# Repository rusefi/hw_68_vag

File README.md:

# hw_68_vag

[Forum Thread](https://rusefi.com/forum/viewtopic.php?f=4&t=1725)

https://github.com/rusefi/rusefi/tree/master/hardware/966595-1_and_963356-1-connector meets https://rusefi.com/forum/viewtopic.php?f=3&t=699

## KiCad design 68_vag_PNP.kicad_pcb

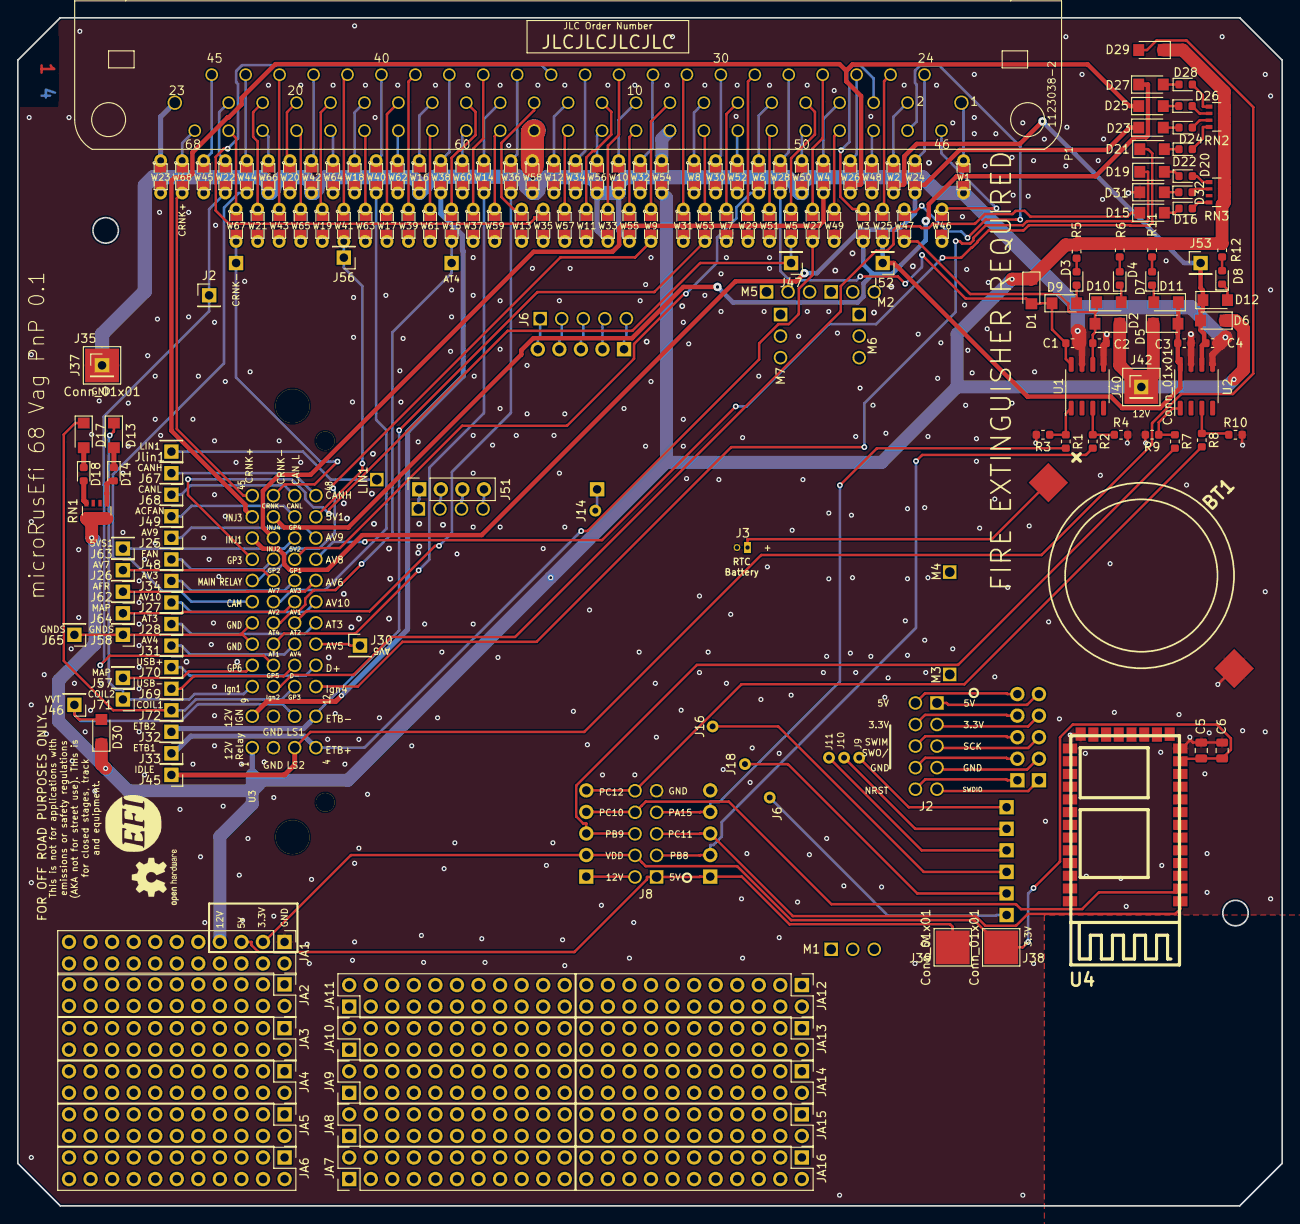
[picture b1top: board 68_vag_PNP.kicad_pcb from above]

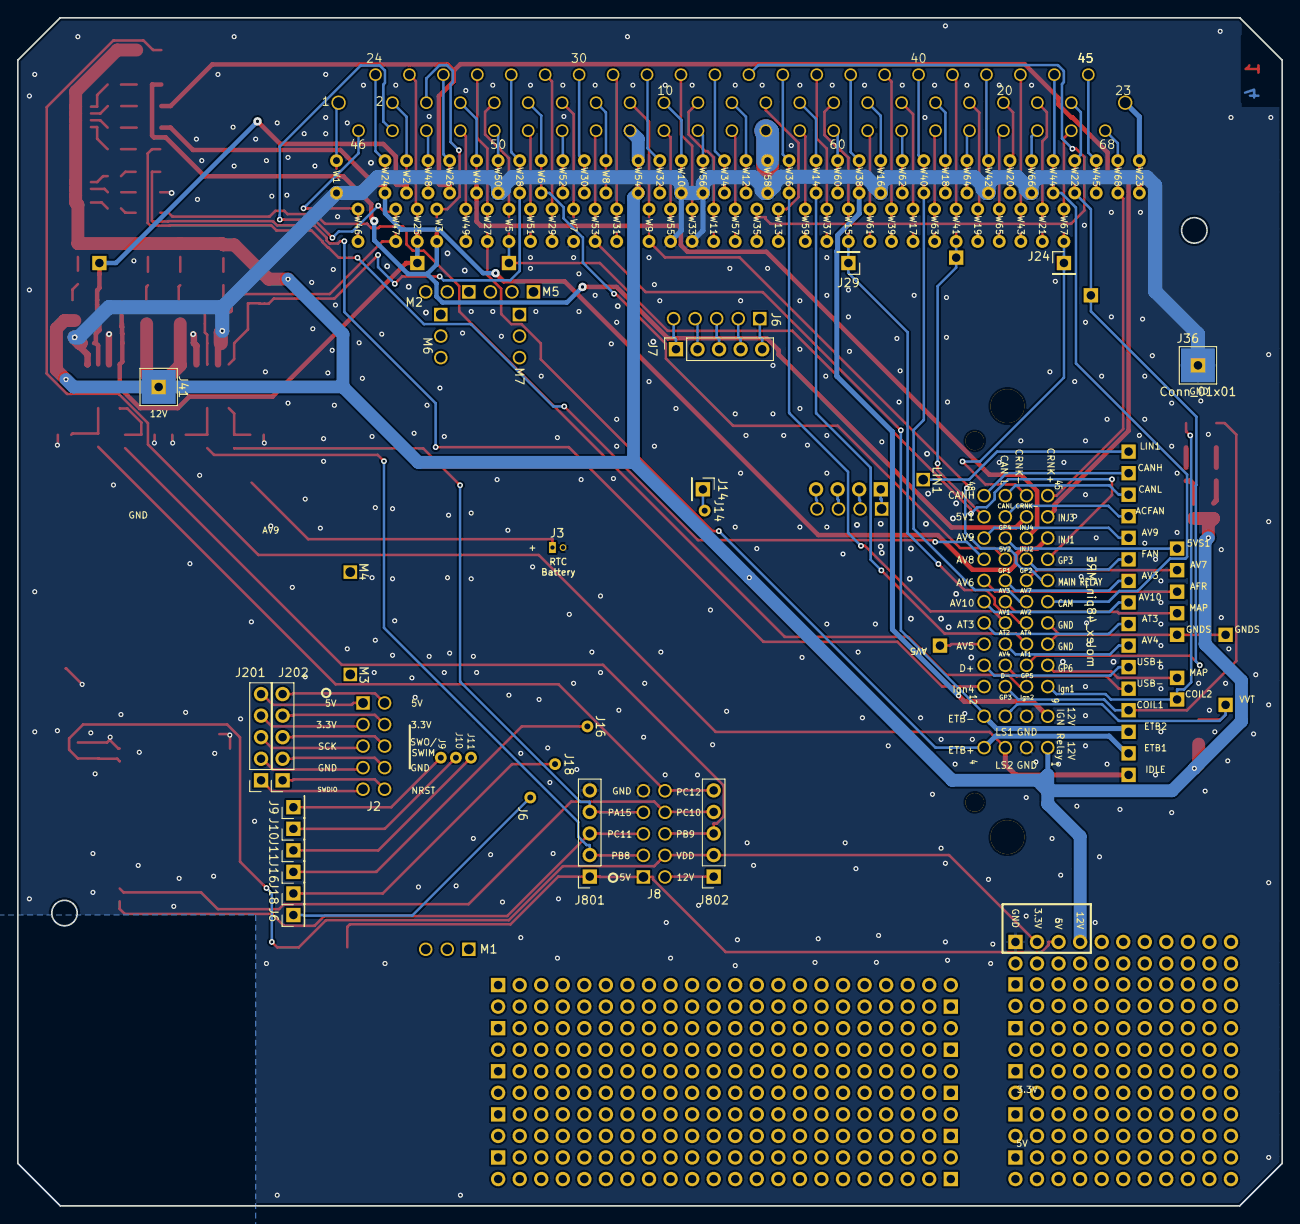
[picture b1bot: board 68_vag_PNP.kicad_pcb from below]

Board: 2 copper layers, 149.0 x 140.0 mm, 201 parts (16 on the bottom side), 185 nets.

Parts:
BT1: Battery_Cell; BATT_CR2032_MPD
C1, C2, C3, C4: 6.8n; C_0603_1608Metric
C5: 0.1u; C_0805_2012Metric
C6: 1u; C_0805_2012Metric
D1, D2, D5, D6, D9, D10, D11, D12, D13, D15, D17, D19, D21, D23, D25, D27, D29, D30, D31: D_Schottky; D_SMF
D3, D4, D7, D8, D14, D16, D18, D20, D22, D24, D26, D28, D32: LED; LED_0603_1608Metric
G1: Disclaimer; Off_Road_Disclaimer
J2, J6, J9, J10, J11, J14, J16, J18, J24, J25, J26, J27, J28, J29, J30, J31, J32, J33, J34, J35, J42, J45, J46, J47, J48, J49, J52, J53, J56, J57, J58, J62, J63, J64, J65, J67, J68, J69, J70, J71, J72: Conn_01x01; PinHeader_1x01_P2.54mm_Vertical
J7, J201, J202, J801, J802: Conn_01x05; PinSocket_1x05_P2.54mm_Vertical
J36, J37, J38, J39, J40, J41: Conn_01x01; TestPoint_Pad_4.0x4.0mm
J51: Conn_01x05; PinSocket_1x04_P2.54mm_Vertical
JA1, JA2, JA3, JA4, JA5, JA6, JA7, JA8, JA9, JA10, JA11, JA12, JA13, JA14, JA15, JA16: Conn_02x11_Odd_Even; PinHeader_2x11_P2.54mm_Vertical
Jlin1: Conn_01x01; PinHeader_1x01_P2.54mm_Vertical
LOGO1: LOGO
LOGO2: LOGO; JLC_PCB_TAG
LOGO3: LOGO; OSHW-Logo2_7.3x6mm_SilkScreen
P1: 1123038-2; 963356-1
R1, R2, R5, R6, R7, R8, R11, R12: 1k; R_0603_1608Metric
R3, R4, R9, R10: 10k; R_0603_1608Metric
RN1, RN2, RN3: 10k; R_Array_Convex_4x0603
U1, U2: VNLD5090; SO-8_3.9x4.9mm_P1.27mm
U3: molex_48pin_MRE; Molex_48_MRE
U4: ITEAD_HC-05
W1, W2, W3, W4, W5, W6, W7, W8, W9, W10, W11, W12, W13, W14, W15, W16, W17, W18, W19, W20, W21, W22, W23, W24, W25, W26, W27, W28, W29, W30, W31, W32, W33, W34, W35, W36, W37, W38, W39, W40, W41, W42, W43, W44, W45, W46, W47, W48, W49, W50, W51, W52, W53, W54, W55, W56, W57, W58, W59, W60, W61, W62, W63, W64, W65, W66, W67, W68: TestPoint_2Pole; SM0805_jumper

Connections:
+12V: D1.1, D2.1, D5.1, D6.1, D29.1, D30.1, J40.1, J41.1, J42.1, JA1.7, R5.2, R6.1, R11.2, R12.1, RN1.1, RN1.2, RN1.3, RN1.4, RN2.1, RN2.2, RN2.3, RN2.4, RN3.1, RN3.2, RN3.3, RN3.4, U3.1, W54.2
/5V_SENS1: J56.1, U3.44, W41.2
/5V_SENS2: J63.1, U3.39
/12_IGN_KEY: U3.5, W38.2
/AC_FAN: J49.1, U3.43
/AFR: J62.1, U3.32
/ALTERNATOR: J57.1, U3.13
/AT3_UNUSED: J28.1, U3.24
/AT4: J29.1, U3.22, W15.2
/AV3_UNUSED: J34.1, U3.31
/AV4_UNUSED: J31.1, U3.19
/AV5_UNUSED: J30.1, U3.20
/AV7_UNUSED: J26.1, U3.30
/AV8_UNUSED: D21.1, U3.36
/AV9_UNUSED: J25.1, U3.40
/AV10_UNUSED: J27.1, U3.28
/CAM: U3.25, W44.2
/CAN_H: J67.1, U3.48
/CAN_L: J68.1, U3.47
/CLT: U3.18, W14.2
/COIL1: D13.1, J71.1, U3.9
/COIL2: D17.1, J72.1, U3.11
/CRANK+: U3.45, W68.2
/CRANK-: J24.1, U3.46, W67.2
/ETB1: J33.1, U3.4, W27.2
/ETB2: J32.1, U3.8, W53.2
/FAN: J48.1, U3.34
/FUEL_RELAY: U3.35, W6.2
/GND_SENS: J58.1, J65.1, U3.17, U3.21
/HI2_UNUSED: D15.1, U3.10
/HI4_UNUSED: D19.1, U3.12
/IAT: U3.23, W36.2
/IDLE: D29.2, J45.1, U3.3
/INJ1: D23.1, U3.37, W24.2
/INJ2: U3.38, W4.2
/INJ3: D25.1, U3.41, W26.2
/INJ4: D27.1, U3.42, W3.2
/INJ5: C3.1, D5.2, D11.1, J52.1, U2.8, W25.2
/INJ6: C4.1, D6.2, D12.1, J53.1, U2.6, W2.2
/J201: J201.5, U3.J201
/J202: J202.5, U3.J202
/J203: J201.4, U3.J203
/J204: J202.4, U3.J204
/J205: J201.3, U3.J205
/J206: J202.3, U3.J206
/J207: J201.2, U3.J207
/J208: J202.2, U3.J208
/J209: J201.1, U3.J209
/J210: J202.1, U3.J210
/J801_5V: J39.1, J801.1, JA1.5, U3.J801
/J802_12V: J802.1, U3.J802
/J803_PB8: J801.2, R2.2, U3.J803
/J804_3.3V: C5.2, C6.1, J38.1, J802.2, JA1.3, U3.J804, U4.12
/J805_PC11: J801.3, U3.J805, U4.1
/J806_PB9: J802.3, R7.2, U3.J806
/J807_PA15: J801.4, R1.2, U3.J807
/J808_PC10: J802.4, U3.J808, U4.2
/J810_PC12: J802.5, R8.2, U3.J810
/MAIN_RELAY_CONTROL: U3.29, W9.2
/MAP: J64.1, U3.27
/MIL: J47.1, U3.33, W5.2
/O2-1Heat: C1.1, D1.2, D9.1, U1.8, W28.2
/O2-2Heat: C2.1, D2.2, D10.1, U1.6, W47.2
/TACH: J2.1, U3.14, W22.2
/TPS: U3.26, W40.2
/USBD+: J70.1, U3.16
/USBD-: J69.1, U3.15
/VBAT: BT1.1, U3.J31
/VVT: D30.2, J46.1, U3.7
GND: BT1.2, C1.2, C2.2, C3.2, C4.2, C5.1, C6.2, D31.1, J35.1, J36.1, J37.1, J801.5, JA1.1, R3.2, R4.2, R9.2, R10.2, U1.5, U1.7, U2.5, U2.7, U3.2, U3.6, U3.J32, U3.J809, U4.13, U4.21, U4.22, W1.2, W7.2, W10.2, W16.2, W33.2, W42.2, W50.2, W55.2, W56.2, W58.2, W66.2
unnamed: D3.1, D9.2
unnamed: D3.2, R5.1
unnamed: D4.2, R6.2
unnamed: D7.2, R11.1
unnamed: D8.2, R12.2
unnamed: D4.1, D10.2
unnamed: D7.1, D11.2
unnamed: D8.1, D12.2
unnamed: D13.2, D14.1
unnamed: D14.2, RN1.5
unnamed: D15.2, D16.1
unnamed: D16.2, RN3.8
unnamed: D17.2, D18.1
unnamed: D18.2, RN1.8
unnamed: D19.2, D20.1
unnamed: D20.2, RN3.5
unnamed: D21.2, D22.1
unnamed: D22.2, RN2.8
unnamed: D23.2, D24.1
unnamed: D24.2, RN2.7
unnamed: D25.2, D26.1
unnamed: D26.2, RN2.6
unnamed: D27.2, D28.1
unnamed: D28.2, RN2.5
unnamed: D31.2, D32.1
unnamed: D32.2, RN3.6
unnamed: J6.1, U3.J6
unnamed: J7.1, U3.J65
unnamed: J7.2, U3.J64
unnamed: J7.3, U3.J63
unnamed: J7.4, U3.J62
unnamed: J7.5, U3.J61
unnamed: J9.1, U3.J9
unnamed: J10.1, U3.J10
unnamed: J11.1, U3.J11
unnamed: J14.1, U3.J14
unnamed: J16.1, U3.J16
unnamed: J18.1, U3.J18
unnamed: J51.1, U3.J51
unnamed: J51.2, U3.J52
unnamed: J51.3, U3.J53
unnamed: J51.4, U3.J54
unnamed: Jlin1.1, U3.LIN1
unnamed: P1.1, W1.1
unnamed: P1.2, W2.1
unnamed: P1.3, W3.1
unnamed: P1.4, W4.1
unnamed: P1.5, W5.1
unnamed: P1.6, W6.1
unnamed: P1.7, W7.1
unnamed: P1.8, W8.1
unnamed: P1.9, W9.1
unnamed: P1.10, W10.1
unnamed: P1.11, W11.1
unnamed: P1.12, W12.1
unnamed: P1.13, W13.1
unnamed: P1.14, W14.1
unnamed: P1.15, W15.1
unnamed: P1.16, W16.1
unnamed: P1.17, W17.1
unnamed: P1.18, W18.1
unnamed: P1.19, W19.1
unnamed: P1.20, W20.1
unnamed: P1.21, W21.1
unnamed: P1.22, W22.1
unnamed: P1.23, W23.1
unnamed: P1.24, W24.1
unnamed: P1.25, W25.1
unnamed: P1.26, W26.1
unnamed: P1.27, W27.1
unnamed: P1.28, W28.1
unnamed: P1.29, W29.1
unnamed: P1.30, W30.1
unnamed: P1.31, W31.1
unnamed: P1.32, W32.1
unnamed: P1.33, W33.1
unnamed: P1.34, W34.1
unnamed: P1.35, W35.1
unnamed: P1.36, W36.1
unnamed: P1.37, W37.1
unnamed: P1.38, W38.1
unnamed: P1.39, W39.1
unnamed: P1.40, W40.1
unnamed: P1.41, W41.1
unnamed: P1.42, W42.1
unnamed: P1.43, W43.1
unnamed: P1.44, W44.1
unnamed: P1.45, W45.1
unnamed: P1.46, W46.1
unnamed: P1.47, W47.1
unnamed: P1.48, W48.1
unnamed: P1.49, W49.1
unnamed: P1.50, W50.1
unnamed: P1.51, W51.1
unnamed: P1.52, W52.1
unnamed: P1.53, W53.1
unnamed: P1.54, W54.1
unnamed: P1.55, W55.1
unnamed: P1.56, W56.1
unnamed: P1.57, W57.1
unnamed: P1.58, W58.1
unnamed: P1.59, W59.1
unnamed: P1.60, W60.1
unnamed: P1.61, W61.1
unnamed: P1.62, W62.1
unnamed: P1.63, W63.1
unnamed: P1.64, W64.1
unnamed: P1.65, W65.1
unnamed: P1.66, W66.1
unnamed: P1.67, W67.1
unnamed: P1.68, W68.1
unnamed: R1.1, R3.1, U1.1
unnamed: R2.1, R4.1, U1.3
unnamed: R7.1, R9.1, U2.1
unnamed: R8.1, R10.1, U2.3

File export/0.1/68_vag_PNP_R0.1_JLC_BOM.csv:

Comment,Designator,Footprint,LCSC, LCSC, MFG,MFG#, Vend1,Vend1#
"Battery_Cell","BT1","rusEFI_Modules:BATT_CR2032_MPD",""
"6.8n","C1,C2,C3,C4","Capacitor_SMD:C_0603_1608Metric","","C1631","KE MET,C0603C682K1RACTU","DIGI,399-3187-1-ND"
"0.1u","C5","Capacitor_SMD:C_0805_2012Metric","","C49678","",""
"1u","C6","Capacitor_SMD:C_0805_2012Metric","","C28323","",""
"D_Schottky","D13,D15,D17,D19,D21,D23,D25,D27,D30,D29,D31,D1,D2,D9,D10,D5,D6,D11,D12","Diode_SMD:D_SMF","","C64898","DIODES_INC,SBR2U60S1F","DIGI,SBR2U60S1F-7DICT-ND"
"LED","D14,D18,D20,D22,D24,D26,D28,D16,D32,D4,D3,D8,D7","LED_SMD:LED_0603_1608Metric","","C2286","DIALIGHT,598-8010-107F","DIGI,350-2029-1-ND"
"Disclaimer","G1","rusEFI_Modules:Off_Road_Disclaimer",""
"Conn_01x01","J40,J39,J38,J37,J36,J41","TestPoint:TestPoint_Pad_4.0x4.0mm",""
"Conn_01x05","J51","Connector_PinSocket_2.54mm:PinSocket_1x04_P2.54mm_Vertical",""
"Conn_01x05","J7,J801,J802,J201,J202","Connector_PinSocket_2.54mm:PinSocket_1x05_P2.54mm_Vertical",""
"Conn_02x11_Odd_Even","JA1,JA2,JA3,JA4,JA5,JA6,JA7,JA8,JA9,JA10,JA11,JA12,JA13,JA14,JA15,JA16","Connector_PinHeader_2.54mm:PinHeader_2x11_P2.54mm_Vertical",""
"Conn_01x01","Jlin1,J24,J25,J26,J27,J28,J29,J30,J31,J32,J33,J34,J35,J2,J56,J45,J46,J47,J48,J49,J58,J71,J72,J62,J63,J64,J67,J68,J69,J70,J57,J65,J6,J18,J9,J10,J11,J16,J14,J53,J52,J42","Connector_PinHeader_2.54mm:PinHeader_1x01_P2.54mm_Vertical",""
"LOGO","LOGO1","rusEFI_Modules:LOGO",""
"LOGO","LOGO2","rusEFI_Modules:JLC_PCB_TAG",""
"LOGO","LOGO3","Symbol:OSHW-Logo2_7.3x6mm_SilkScreen",""
"1123038-2","P1","rusEFI_Modules:963356-1",""
"1k","R1,R2,R6,R5,R7,R8,R12,R11","Resistor_SMD:R_0603_1608Metric","","C21190","YAGEO,RC0603JR-071KL","DIGI,311-1.0KGRCT-ND"
"10k","R4,R3,R10,R9","Resistor_SMD:R_0603_1608Metric","","C25804","YAGEO,RC0603JR-0710KL","DIGI,311-10KGRCT-ND"
"10k","RN2,RN3,RN1","Resistor_SMD:R_Array_Convex_4x0603","","C29718","YAGEO,YC164-JR-0710KL","DIGI,YC164J-10KCT-ND"
"VNLD5090","U1,U2","Package_SO:SO-8_3.9x4.9mm_P1.27mm","","C377942","ST,VNLD5090TR-E","DIGI,497-14323-1-ND"
"molex_48pin_MRE","U3","rusEFI_Modules:Molex_48_MRE",""
"ITEAD_HC-05","U4","rusEFI_Modules:ITEAD_HC-05",""
"TestPoint_2Pole","W23,W54,W58,W60,W61,W62,W63,W64,W65,W66,W67,W68,W59,W57,W56,W55,W39,W43,W45,W46,W47,W48,W49,W50,W51,W52,W53,W44,W42,W41,W40,W24,W28,W30,W31,W32,W33,W34,W35,W36,W37,W38,W29,W27,W26,W25,W8,W12,W14,W15,W16,W17,W18,W19,W20,W21,W22,W13,W11,W10,W9,W2,W6,W7,W5,W4,W3,W1","rusEFI_Modules:SM0805_jumper","","C17477","",""

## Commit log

2020-04-28 submodule
2020-05-06 Draft
2020-05-10 fresh lib
2020-05-13 connected idle to ETB
2020-05-14 Updated hole locations.
2020-06-14 R0.1 draft, pre-auto-route
2020-06-15 Added CPL file and script.
2020-06-17 Updated the script, fixed rotation.
2020-06-17 Updated file name.
2020-06-17 ibom
2020-06-17 Took a working script and made it not work.
2020-06-17 dimentions
2020-06-17 Updated the dimentions on the CmtsUser layer.
2020-06-18 Script now converts a KC POS file directly to a CPL for JLC.
2020-06-18 Added draft copy of CPL script.
2020-06-18 FAILED ATTEMPT to link dialog file name with original script. See line 148 for my failed attempt.
2020-08-16 # this file is related to https://github.com/rusefi/kicad-libraries/blob/master/generate_diffs.sh
